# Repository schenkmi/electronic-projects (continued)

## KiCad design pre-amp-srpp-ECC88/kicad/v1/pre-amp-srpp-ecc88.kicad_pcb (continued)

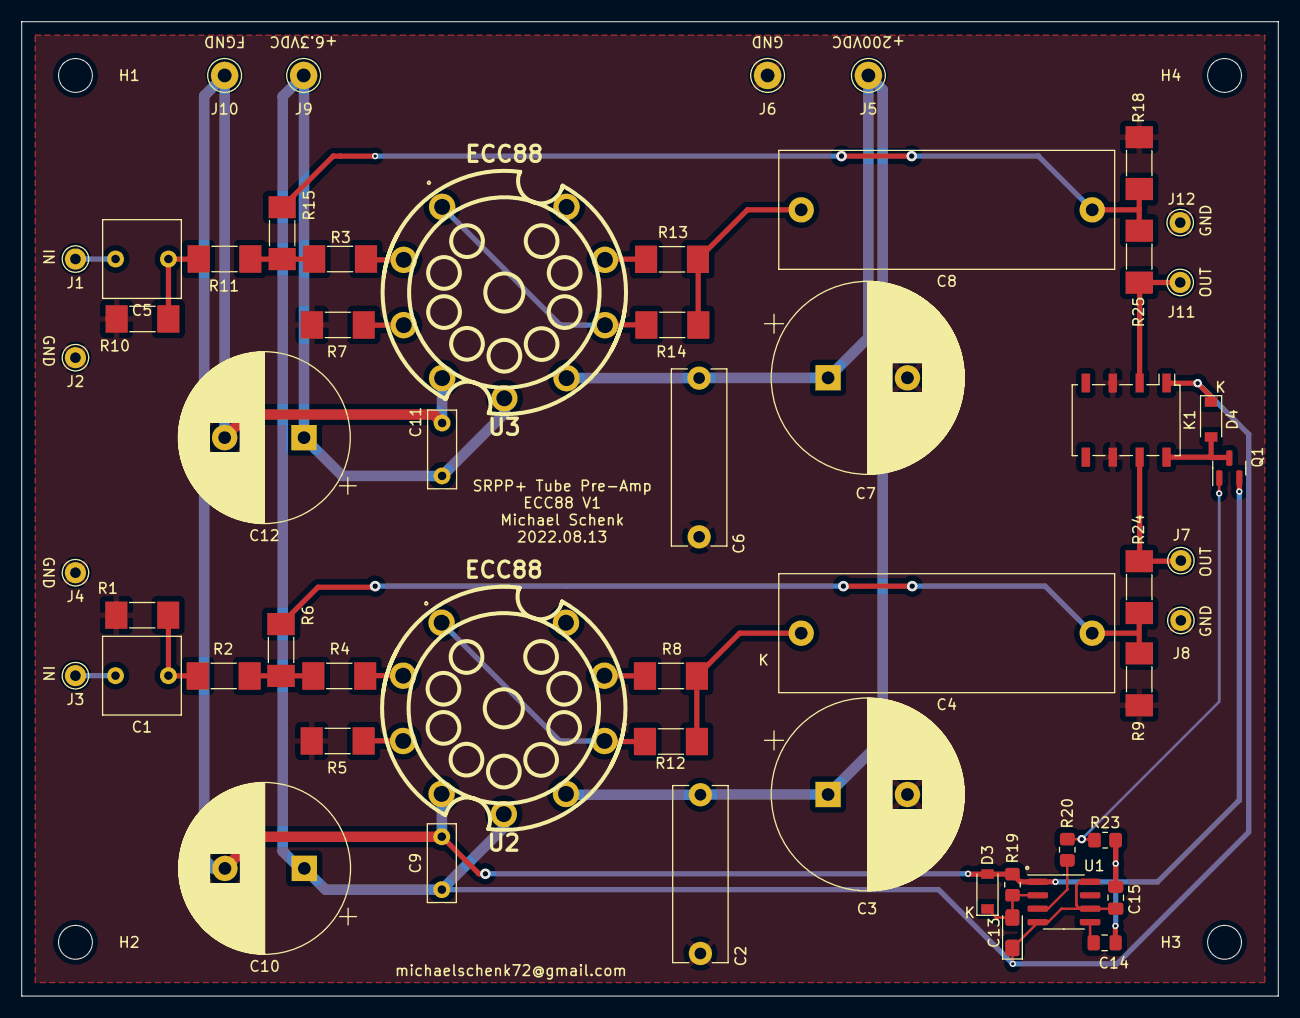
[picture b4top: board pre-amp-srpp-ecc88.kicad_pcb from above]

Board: 2 copper layers, 118.7 x 92.1 mm, 59 parts (0 on the bottom side), 29 nets.
